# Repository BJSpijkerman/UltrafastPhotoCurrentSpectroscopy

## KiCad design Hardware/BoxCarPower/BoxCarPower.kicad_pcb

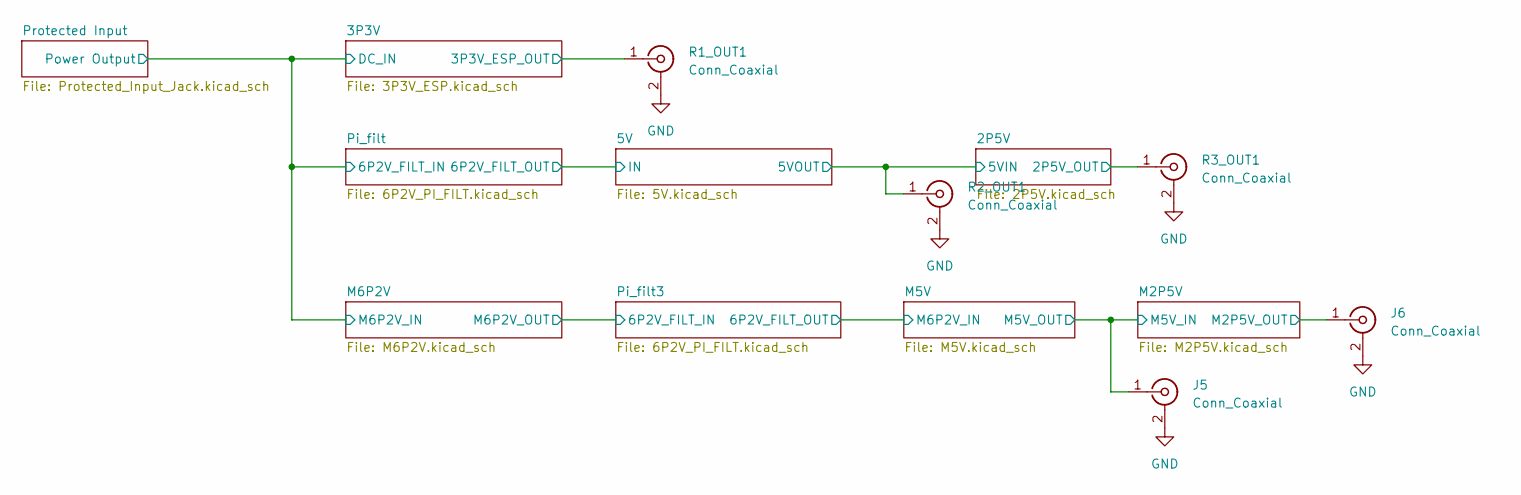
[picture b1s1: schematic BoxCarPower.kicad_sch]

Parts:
J5, J6: Conn_Coaxial; SMA_Amphenol_132289_EdgeMount
R1_OUT1, R2_OUT1, R3_OUT1: Conn_Coaxial; SMA_Amphenol_132289_EdgeMount

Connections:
/2P5V/2P5V_OUT: R3_OUT1.1 (In); also elsewhere on the board
/2P5V/5VIN: R2_OUT1.1 (In); also elsewhere on the board
/3P3V/3P3V_ESP_OUT: R1_OUT1.1 (In); also elsewhere on the board
/M2P5V/M2P5V_OUT: J6.1 (In); also elsewhere on the board
/M2P5V/M5V_IN: J5.1 (In); also elsewhere on the board
GND: J5.2 (Ext), J6.2 (Ext), R1_OUT1.2 (Ext), R2_OUT1.2 (Ext), R3_OUT1.2 (Ext); also elsewhere on the board

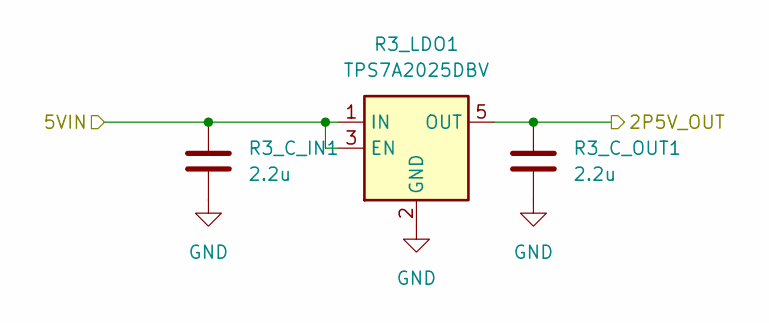
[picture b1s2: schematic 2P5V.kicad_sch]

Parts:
R3_C_IN1, R3_C_OUT1: 2.2u; C_1206_3216Metric
R3_LDO1: TPS7A2025DBV; SOT-23-5

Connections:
/2P5V/2P5V_OUT: R3_C_OUT1.1, R3_LDO1.5 (OUT); also elsewhere on the board
/2P5V/5VIN: R3_C_IN1.1, R3_LDO1.1 (IN), R3_LDO1.3 (EN); also elsewhere on the board
GND: R3_C_IN1.2, R3_C_OUT1.2, R3_LDO1.2 (GND); also elsewhere on the board

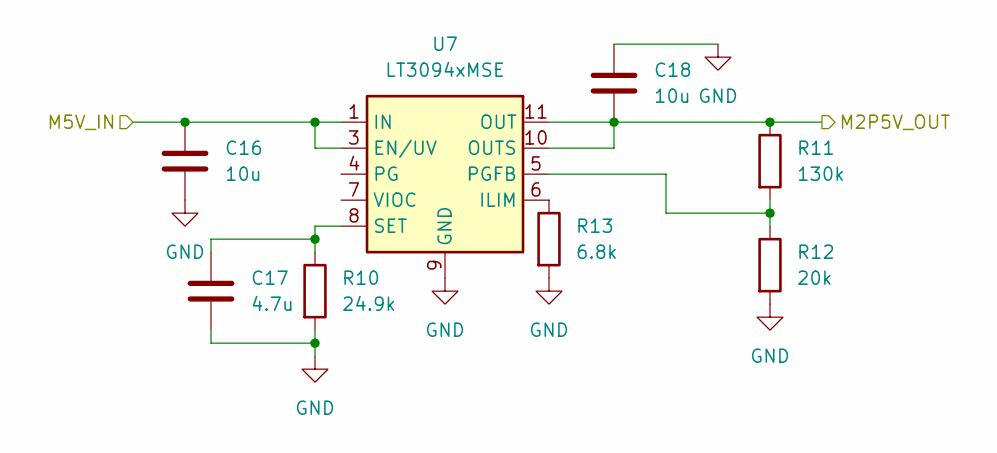
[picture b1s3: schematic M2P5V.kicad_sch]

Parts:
C16, C18: 10u; C_0805_2012Metric
C17: 4.7u; C_1206_3216Metric
R10: 24.9k; R_0603_1608Metric
R11: 130k; R_0603_1608Metric
R12: 20k; R_0603_1608Metric
R13: 6.8k; R_0603_1608Metric
U7: LT3094xMSE; MSOP-12-1EP_3x4.039mm_P0.65mm_EP1.651x2.845mm

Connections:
/M2P5V/M2P5V_OUT: C18.2, R11.1, U7.10 (OUTS), U7.11 (OUT), U7.12 (OUT); also elsewhere on the board
/M2P5V/M5V_IN: C16.1, U7.1 (IN), U7.2 (IN), U7.3 (EN/UV), U7.13 (IN); also elsewhere on the board
GND: C16.2, C17.2, C18.1, R10.2, R12.2, R13.2, U7.9 (GND); also elsewhere on the board
unnamed: R13.1, U7.6 (ILIM)
unnamed: R11.2, R12.1, U7.5 (PGFB)
unnamed: C17.1, R10.1, U7.8 (SET)

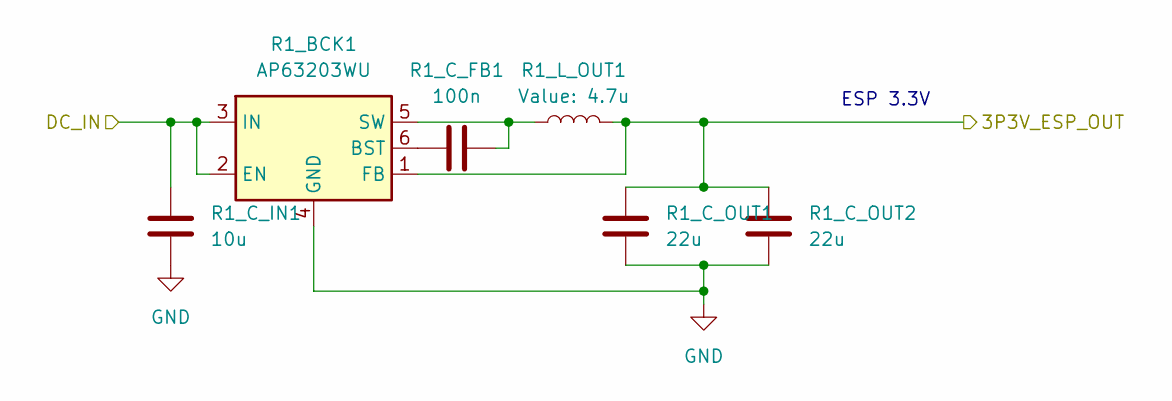
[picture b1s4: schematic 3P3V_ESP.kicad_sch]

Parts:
R1_BCK1: AP63203WU; TSOT-23-6
R1_C_FB1: 100n; C_0603_1608Metric
R1_C_IN1: 10u; C_0805_2012Metric
R1_C_OUT1, R1_C_OUT2: 22u; C_0805_2012Metric
R1_L_OUT1: 4.7u; L_Bourns-SRN4018

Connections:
/3P3V/3P3V_ESP_OUT: R1_BCK1.1 (FB), R1_C_OUT1.1, R1_C_OUT2.1, R1_L_OUT1.2; also elsewhere on the board
/3P3V/DC_IN: R1_BCK1.2 (EN), R1_BCK1.3 (IN), R1_C_IN1.1; also elsewhere on the board
GND: R1_BCK1.4 (GND), R1_C_IN1.2, R1_C_OUT1.2, R1_C_OUT2.2; also elsewhere on the board
unnamed: R1_BCK1.6 (BST), R1_C_FB1.1
unnamed: R1_BCK1.5 (SW), R1_C_FB1.2, R1_L_OUT1.1

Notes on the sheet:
ESP 3.3V

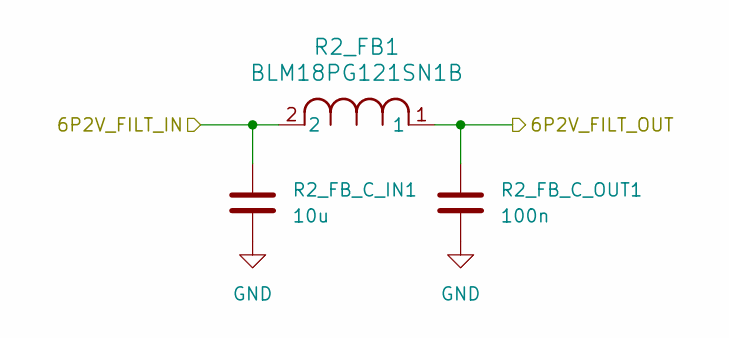
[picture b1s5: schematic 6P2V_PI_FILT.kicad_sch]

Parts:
R2_FB1: BLM18PG121SN1B; L_0603_1608Metric
R2_FB_C_IN1: 10u; C_0805_2012Metric
R2_FB_C_OUT1: 100n; C_0603_1608Metric

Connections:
/3P3V/DC_IN: R2_FB1.2, R2_FB_C_IN1.1; also elsewhere on the board
/5V/IN: R2_FB1.1, R2_FB_C_OUT1.1; also elsewhere on the board
GND: R2_FB_C_IN1.2, R2_FB_C_OUT1.2; also elsewhere on the board

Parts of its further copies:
C47: 10u; C_0805_2012Metric
C48: 100n; C_0603_1608Metric
L6: BLM18PG121SN1B; L_0603_1608Metric

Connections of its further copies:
/M5V/M6P2V_IN: C48.1, L6.1; also elsewhere on the board
/M6P2V/M6P2V_OUT: C47.1, L6.2; also elsewhere on the board
GND: C47.2, C48.2; also elsewhere on the board

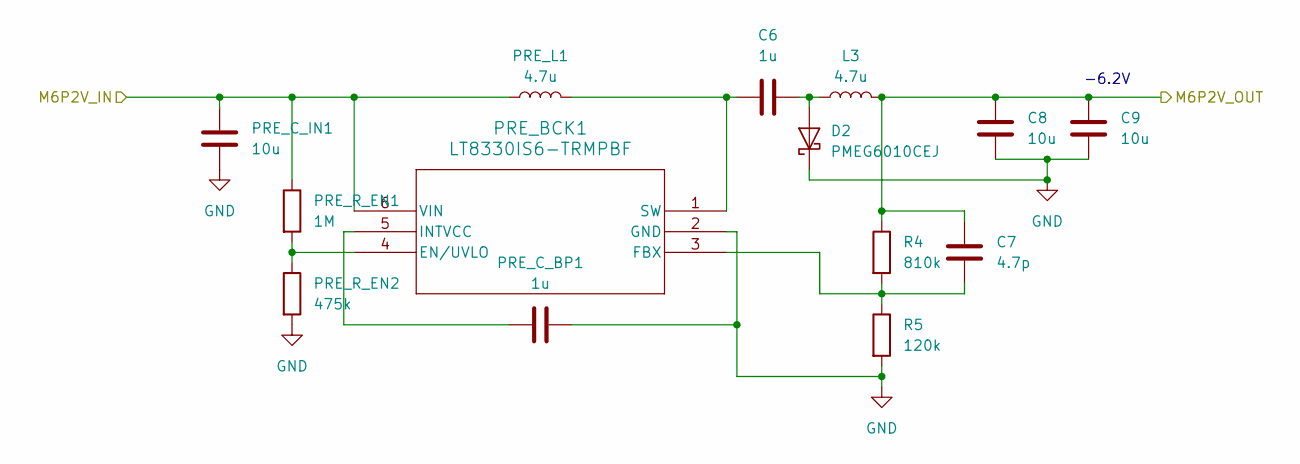
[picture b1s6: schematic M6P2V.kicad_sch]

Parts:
C6: 1u; C_0603_1608Metric
C7: 4.7p; C_0603_1608Metric
C8, C9: 10u; C_0805_2012Metric
D2: PMEG6010CEJ; D_SOD-323F
L3: 4.7u; L_Bourns-SRN4018
PRE_BCK1: LT8330IS6-TRMPBF; IC6_LT8330IS6-TRMPBF_ADI
PRE_C_BP1: 1u; C_0805_2012Metric
PRE_C_IN1: 10u; C_0805_2012Metric
PRE_L1: 4.7u; L_Bourns-SRN4018
PRE_R_EN1: 1M; R_0603_1608Metric
PRE_R_EN2: 475k; R_0603_1608Metric
R4: 810k; R_0603_1608Metric
R5: 120k; R_0603_1608Metric

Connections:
/3P3V/DC_IN: PRE_BCK1.6 (VIN), PRE_C_IN1.1, PRE_L1.1, PRE_R_EN1.1; also elsewhere on the board
/M6P2V/M6P2V_OUT: C7.1, C8.1, C9.1, L3.2, R4.1; also elsewhere on the board
GND: C8.2, C9.2, D2.1 (K), PRE_BCK1.2 (GND), PRE_C_BP1.2, PRE_C_IN1.2, PRE_R_EN2.2, R5.2; also elsewhere on the board
unnamed: C6.2, D2.2 (A), L3.1
unnamed: PRE_BCK1.4 (EN/UVLO), PRE_R_EN1.2, PRE_R_EN2.1
unnamed: C7.2, PRE_BCK1.3 (FBX), R4.2, R5.1
unnamed: PRE_BCK1.5 (INTVCC), PRE_C_BP1.1
unnamed: C6.1, PRE_BCK1.1 (SW), PRE_L1.2

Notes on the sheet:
-6.2V

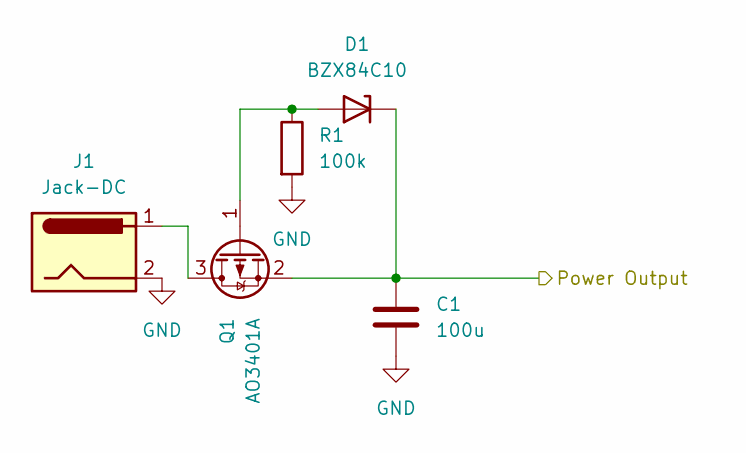
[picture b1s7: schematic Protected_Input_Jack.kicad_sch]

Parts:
C1: 100u; CP_Elec_6.3x7.7
D1: BZX84C10; SOT-23
J1: Jack-DC; BarrelJack_CUI_PJ-102AH_Horizontal
Q1: AO3401A; SOT-23
R1: 100k; R_0603_1608Metric

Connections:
/3P3V/DC_IN: C1.1, D1.3 (K), Q1.2 (S); also elsewhere on the board
GND: C1.2, J1.2, R1.2; also elsewhere on the board
unnamed: D1.1 (A), Q1.1 (G), R1.1
unnamed: J1.1, Q1.3 (D)

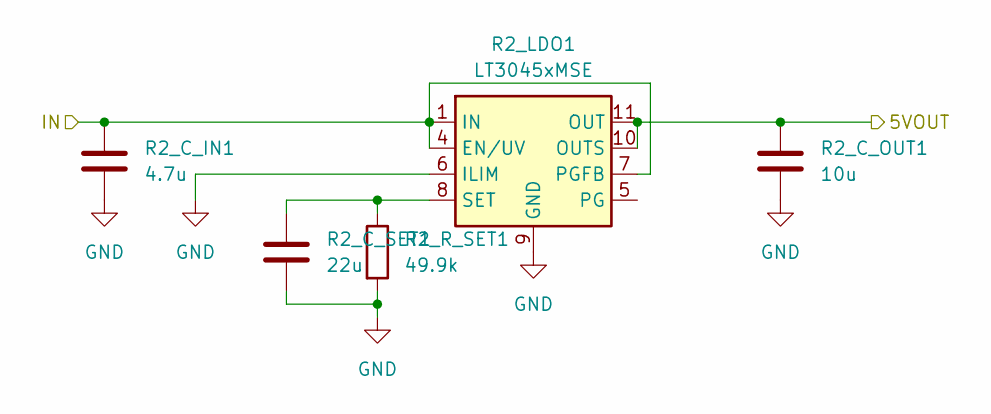
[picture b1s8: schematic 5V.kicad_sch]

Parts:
R2_C_IN1: 4.7u; C_1206_3216Metric
R2_C_OUT1: 10u; C_0805_2012Metric
R2_C_SET1: 22u; C_0805_2012Metric
R2_LDO1: LT3045xMSE; MSOP-12-1EP_3x4.039mm_P0.65mm_EP1.651x2.845mm
R2_R_SET1: 49.9k; R_0603_1608Metric

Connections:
/2P5V/5VIN: R2_C_OUT1.1, R2_LDO1.10 (OUTS), R2_LDO1.11 (OUT), R2_LDO1.12 (OUT); also elsewhere on the board
/5V/IN: R2_C_IN1.1, R2_LDO1.1 (IN), R2_LDO1.2 (IN), R2_LDO1.3 (IN), R2_LDO1.4 (EN/UV), R2_LDO1.7 (PGFB); also elsewhere on the board
GND: R2_C_IN1.2, R2_C_OUT1.2, R2_C_SET1.2, R2_LDO1.6 (ILIM), R2_LDO1.9 (GND), R2_LDO1.13 (GND), R2_R_SET1.2; also elsewhere on the board
unnamed: R2_C_SET1.1, R2_LDO1.8 (SET), R2_R_SET1.1

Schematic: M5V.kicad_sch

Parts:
C13: 4.7u; C_1206_3216Metric
C14, C15: 10u; C_0805_2012Metric
R7: 49.9k; R_0603_1608Metric
R8: 280k; R_0603_1608Metric
R9: 20k; R_0603_1608Metric
R14: 6.8k; R_0603_1608Metric
U5: LT3094xMSE; MSOP-12-1EP_3x4.039mm_P0.65mm_EP1.651x2.845mm

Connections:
/M2P5V/M5V_IN: C14.2, R8.1, U5.10 (OUTS), U5.11 (OUT), U5.12 (OUT); also elsewhere on the board
/M5V/M6P2V_IN: C15.1, U5.1 (IN), U5.2 (IN), U5.3 (EN/UV), U5.13 (IN); also elsewhere on the board
GND: C13.2, C14.1, C15.2, R7.2, R9.2, R14.2, U5.9 (GND); also elsewhere on the board
unnamed: R14.1, U5.6 (ILIM)
unnamed: R8.2, R9.1, U5.5 (PGFB)
unnamed: C13.1, R7.1, U5.8 (SET)

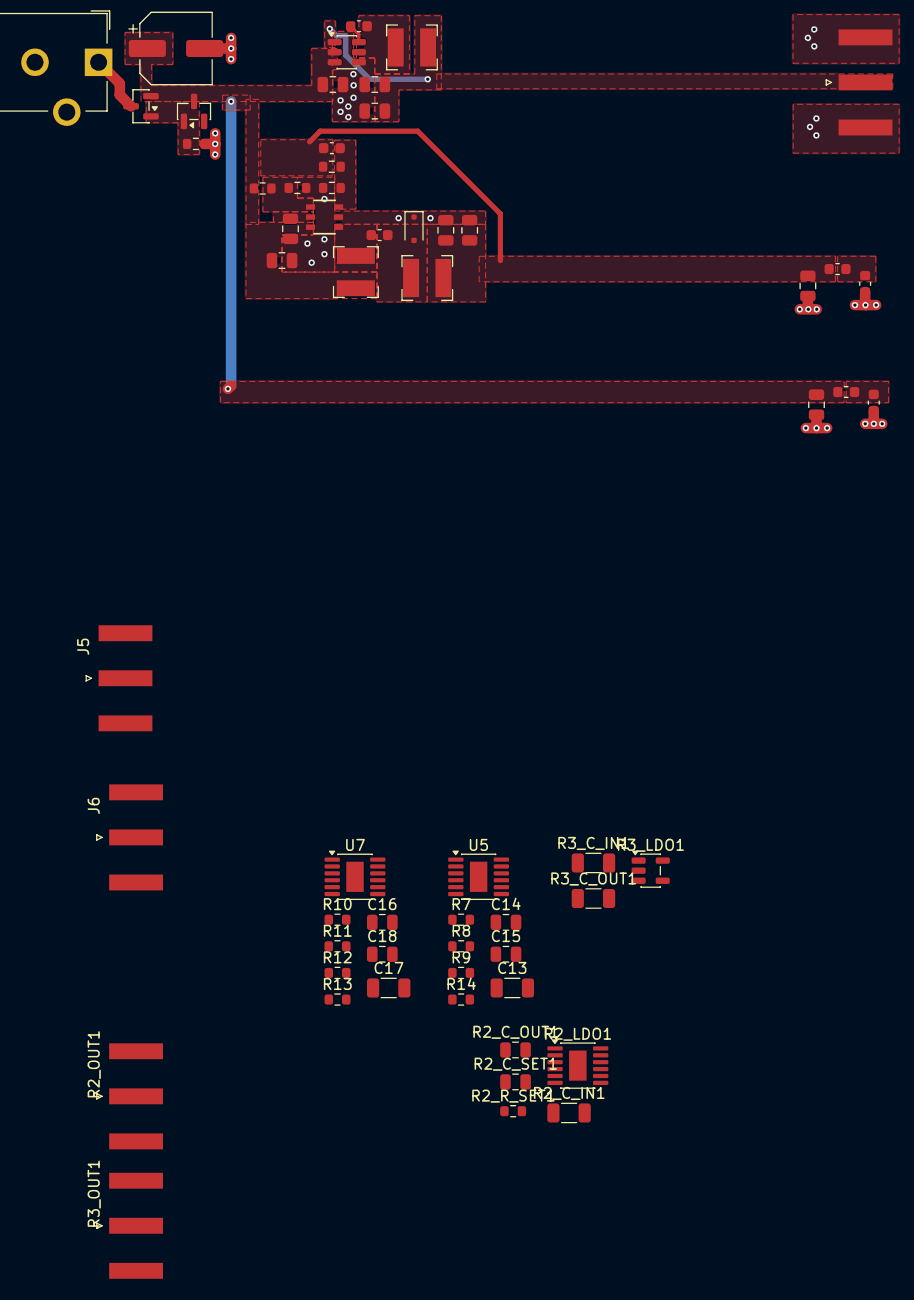
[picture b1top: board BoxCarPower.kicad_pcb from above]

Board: 2 copper layers, 60 parts (0 on the bottom side), 26 nets.

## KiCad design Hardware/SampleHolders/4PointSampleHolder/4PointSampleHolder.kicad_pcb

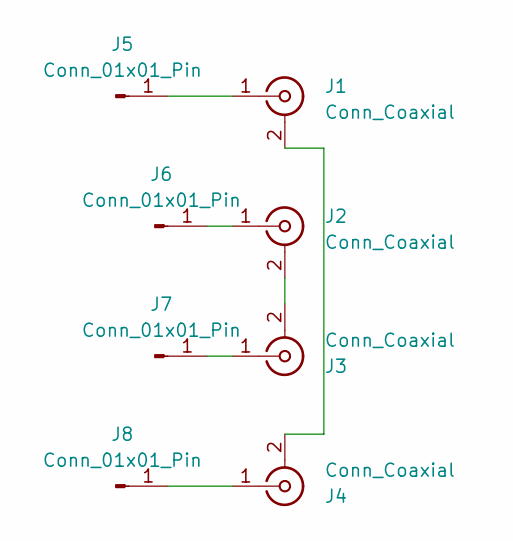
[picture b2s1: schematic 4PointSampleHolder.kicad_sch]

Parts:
J1, J2, J3, J4: Conn_Coaxial; BNC_TEConnectivity_1478035_Horizontal
J5, J6, J7, J8: Conn_01x01_Pin; Untitled

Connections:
unnamed: J1.2 (Ext), J4.2 (Ext)
unnamed: J1.1 (In), J5.1 (Pin_1_1)
unnamed: J2.2 (Ext), J3.2 (Ext)
unnamed: J2.1 (In), J6.1 (Pin_1_1)
unnamed: J3.1 (In), J7.1 (Pin_1_1)
unnamed: J4.1 (In), J8.1 (Pin_1_1)

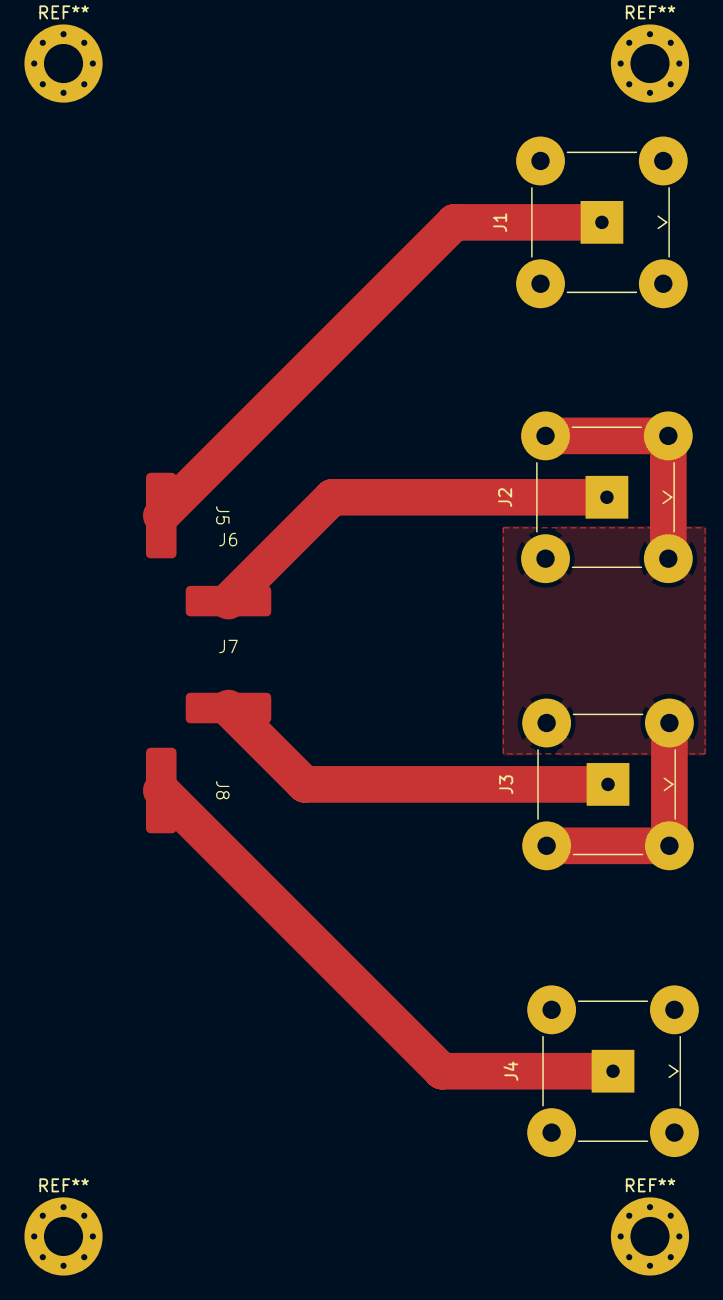
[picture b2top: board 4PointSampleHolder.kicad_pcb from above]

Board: 2 copper layers, 8 parts (0 on the bottom side), 6 nets.
